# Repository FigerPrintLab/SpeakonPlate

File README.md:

# Speakon plate (Stakx)
Input PCB for high power speakers (30A capable) including:
- 4 pole speakON parallel IN (x2)
- 4 pole Phoenix connector OUT
- 4 pole JST connector OUT

## Connectors
[Neutrik NL4MP-M3](https://www.neutrik.com/en/product/nl4mp-m3) (30A RMS, 250V AC)  
[Phoenix ZFKDSA 2,5-5,08- 4](https://www.phoenixcontact.com/online/portal/pi?uri=pxc-oc-itemdetail:pid=1714618&library=pien&tab=1) (24A 400V)  
[JST B4PS-VH](http://www.jst-mfg.com/product/pdf/eng/eVH.pdf?5fdbd93841a69) (10A AC/DC, 250V AC/DC)

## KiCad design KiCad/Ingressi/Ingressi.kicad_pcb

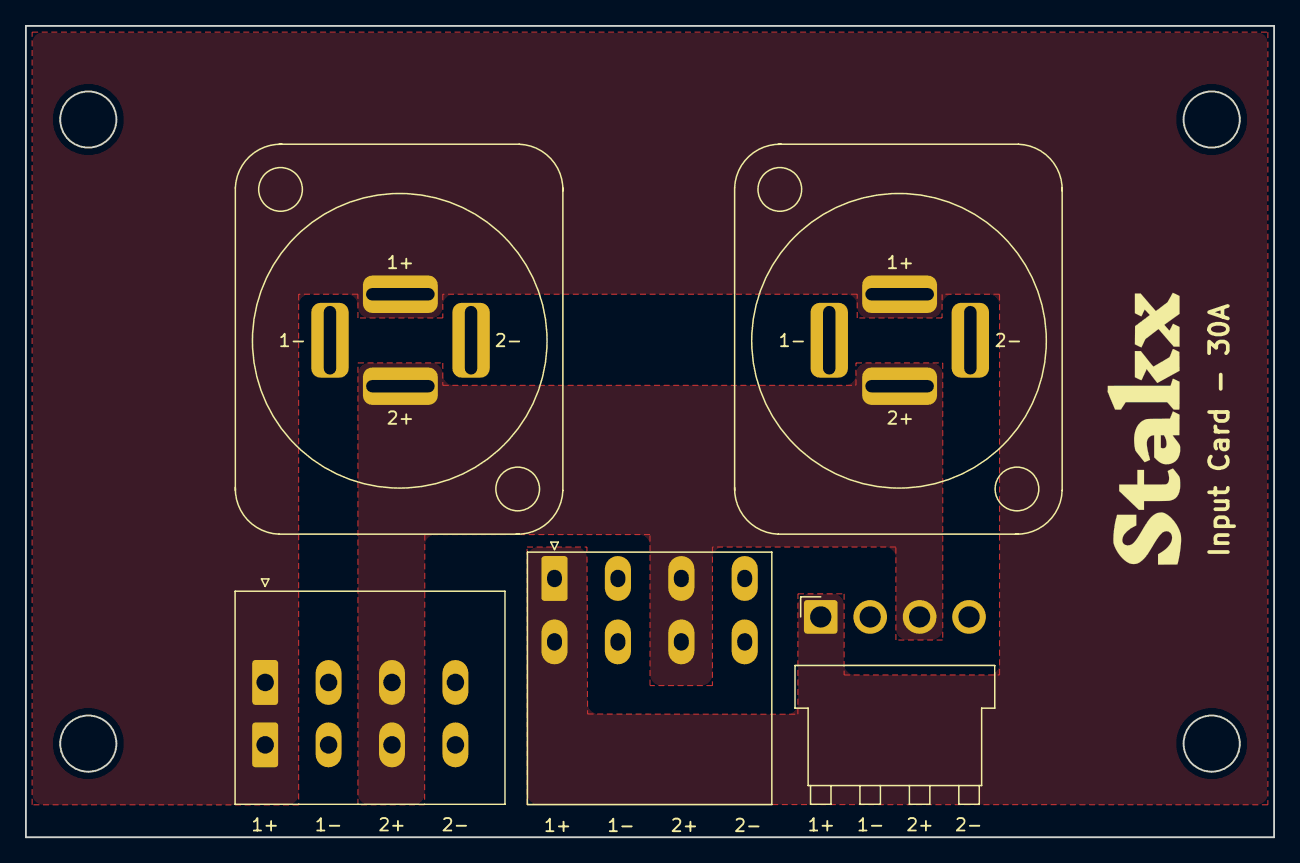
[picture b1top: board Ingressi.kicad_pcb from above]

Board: 2 copper layers, 100.0 x 65.0 mm, 5 parts (0 on the bottom side), 4 nets, no tracks yet.

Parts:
J1, J2: SpeakON_NL4; Jack_speakON_Neutrik_NL4MP
J3: Phoenix; Phoenix_ZFKDSA_2,5_5,08_4
J4: JST; JST_VH_B4PS-VH_1x04_P3.96mm_Horizontal
J5: Faston; Faston_01x04_P5.08mm_D5.08mm

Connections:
unnamed: J1.1+, J2.1+, J3.1, J4.1, J5.1
unnamed: J1.1-, J2.1-, J3.2, J4.2, J5.2
unnamed: J1.2+, J2.2+, J3.3, J4.3, J5.3
unnamed: J1.2-, J2.2-, J3.4, J4.4, J5.4

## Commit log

2020-12-10 update KiCad
2020-12-11 update info JST
2020-12-11 changed Faston to Phoenix
2020-12-11 schematic finished
2020-12-11 Faston changed to Phoenix
2020-12-11 update name
2020-12-11 update PCB
2020-12-12 updated PCB
2020-12-12 updated PCB and gerbers
2020-12-13 added 3D model
2020-12-13 update candidate Phoenix connector
2020-12-14 update cadidate README
2020-12-17 Phoenix connector updated and added gerbers
2020-12-17 updated connector and added gerbers
2020-12-17 update gerbers
2020-12-17 changed JST
2020-12-17 image added
2020-12-17 schematic updated
2020-12-18 added gerbers
2021-01-06 figerprint
2021-06-29 added faston connector
2021-08-11 minor updates
